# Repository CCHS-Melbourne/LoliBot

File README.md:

# LoliBot - The ESP32 Based Soccer bot.

Quick links ...

  * [Hardware assembly](http://www.openhardwareconf.org/wiki/LoliBot-Assembly)
  * [Software installation and usage](software)

Welcome to the 2018 linux.conf.au Open Hardware Project.  You can see information about this and other MiniConfs at <http://www.openhardwareconf.org/wiki/Main_Page>.

If you're attending the assembly workshop at Linux.conf.au 2018, the place to start is <http://www.openhardwareconf.org/wiki/LoliBot>

This year's project is called the Lolibot, and is a simple robot is designed to chase and kick a Ping Pong ball around.

It features a Lolin32-lite ESP32 based chip as it's primary microprocessor and includes a MPU6050 6 axis accelerometer.

In order to reduce complexity and to be a bit more flexible with our design this years project is a platform with discrete components.
Those of you who are looking forward to the smell of melting solder won't be disappointed though, there are many headers, LEDS and switches to keep you busy.

## Hardware

### Screen Shots

### Assembly

Assembly instructions for the kit are at <http://www.openhardwareconf.org/wiki/LoliBot-Assembly>

### Hardware Links

* [WEMOS LOLIN32](https://wiki.wemos.cc/products:lolin32:lolin32)
* [mpu-6050](https://www.invensense.com/products/motion-tracking/6-axis/mpu-6050/) TBD lots of options
* [Wheels](https://www.aliexpress.com/item/TT-Motor-130motor-with-the-wheel-Smart-Car-Robot-Gear-Motor-for-Arduino-DC3V-6V-DC/32829319427.html) one of many like this..

### datasheets

* [L9110 Motor control driver chip](datasheets/datasheet-l9110.pdf)

## Software

All the usual ESP32 development options apply to the LoliBot ...

 * [microPython scripts](software)
 * Arduino IDE sketches
 * Native ESP-IDF FreeRTOS firmware

We've chosen to focus on using microPython to provide a simple, yet
capable entry point for newcomers to robotics and embedded computers.

The [software sub-directory has instructions](software)
 on installing and developing software for the LoliBot.

## LICENSE

Licensed under the TAPR Open Hardware License (<http://www.tapr.org/OHL>). The "license" sub-folder also contains a copy of this license in plain text format.

Copyright John Spencer, Angus Gratton, Andy Gelme, Jon Oxer, Mark Wolfe 2017

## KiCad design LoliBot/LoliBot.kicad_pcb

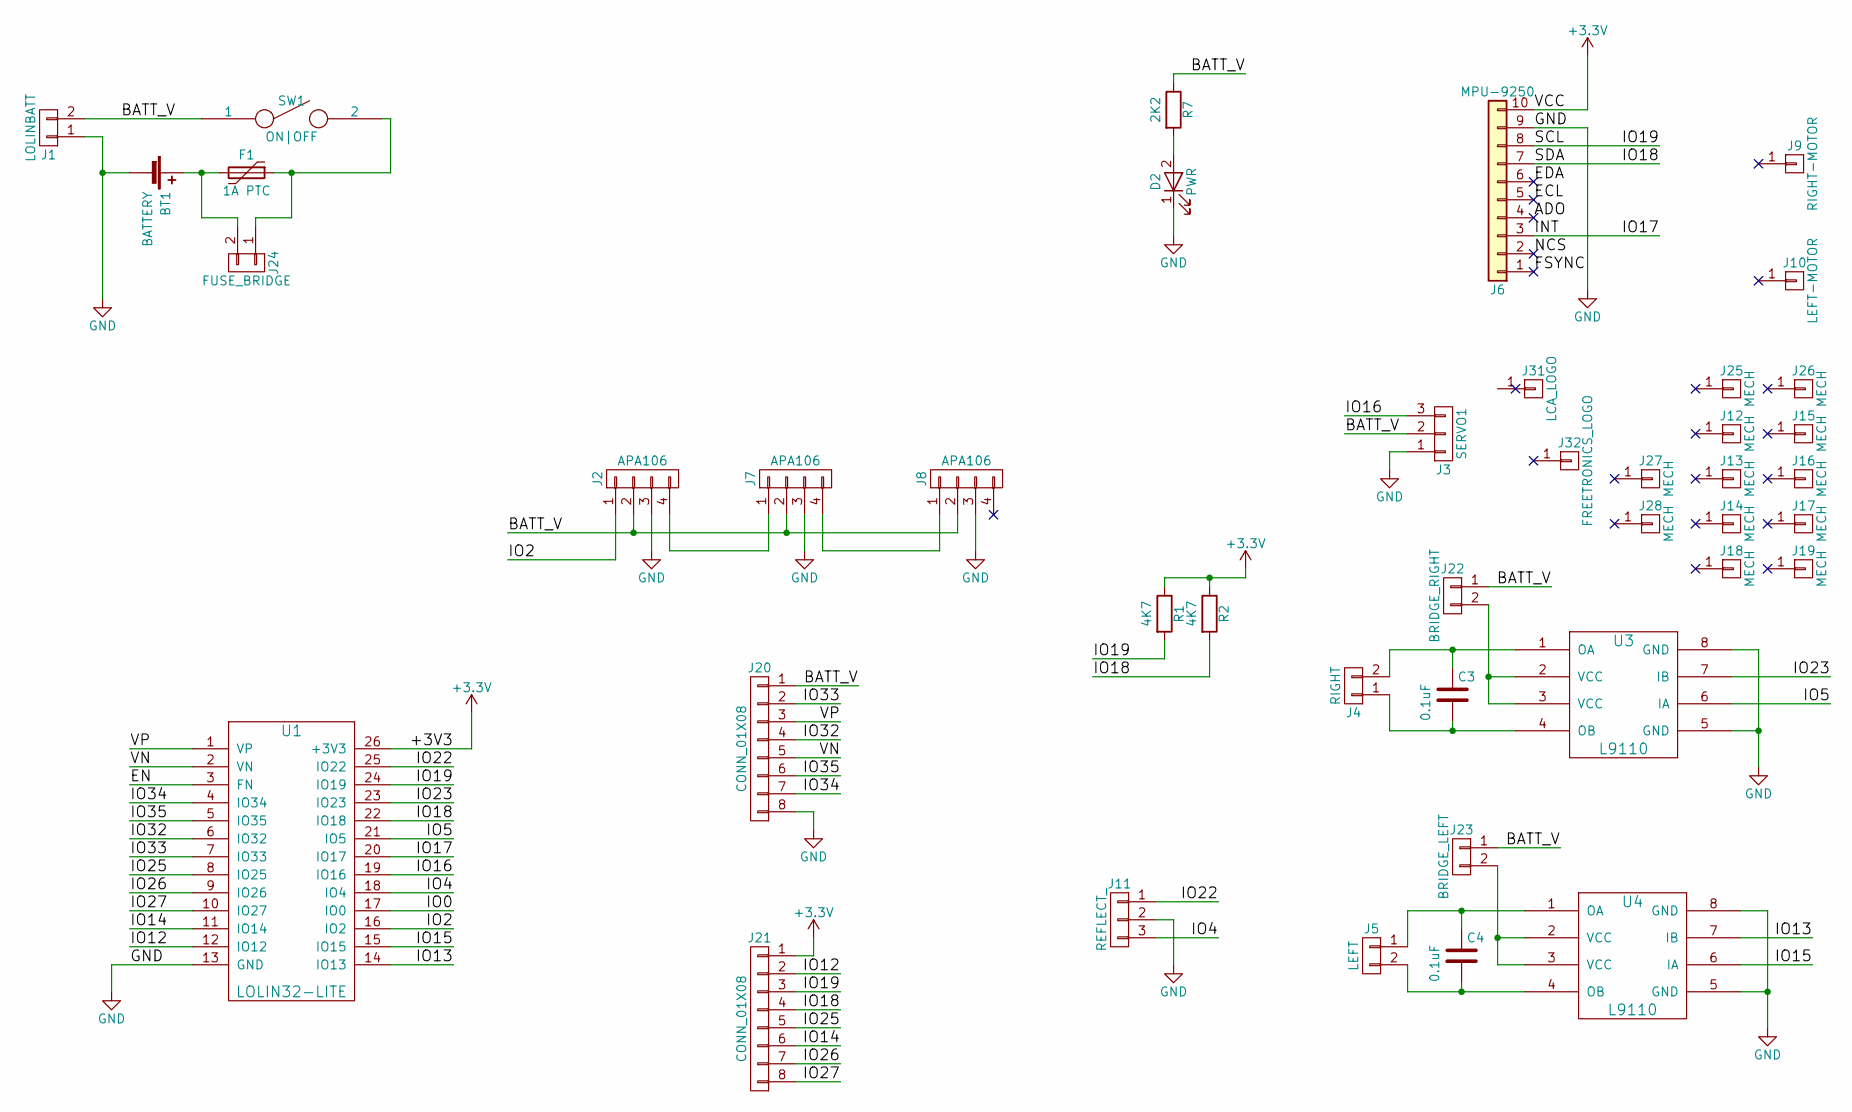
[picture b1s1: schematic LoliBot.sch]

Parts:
BT1: BATTERY; BH-18650
C3, C4: 0.1uF; C_0603_HandSoldering
D2: PWR; LED_D3.0mm
F1: 1A PTC; R_1210_HandSoldering
J1: LOLINBATT; Pin_Header_Straight_1x02_Pitch2.54mm
J2, J7, J8: APA106; LED_8MM_APA-106
J3: SERVO1; Pin_Header_Angled_1x03_Pitch2.54mm
J4: RIGHT; Pin_Header_Straight_1x02_Pitch2.00mm
J5: LEFT; Pin_Header_Straight_1x02_Pitch2.00mm
J6: MPU-9250; Pin_Header_Straight_1x10_Pitch2.54mm
J9: RIGHT-MOTOR; DC-Motor
J10: LEFT-MOTOR; DC-Motor
J11: REFLECT_; Pin_Header_Straight_1x03_Pitch2.54mm
J12, J13, J14, J15, J16, J17, J18, J19, J25, J26, J27, J28: MECH; MountingHole_3.2mm_M3_Pad
J20, J21: CONN_01X08; Pin_Header_Straight_2x04_Pitch2.54mm
J22: BRIDGE_RIGHT; Pin_Header_Straight_1x02_Pitch2.54mm
J23: BRIDGE_LEFT; Pin_Header_Straight_1x02_Pitch2.54mm
J24: FUSE_BRIDGE; bridge
J31: LCA_LOGO; LCA2018_LOGO
J32: FREETRONICS_LOGO; LOGO_FREETRONICS_33mm
R1, R2: 4K7; R_0603_HandSoldering
R7: 2K2; R_0603_HandSoldering
SW1: ON|OFF; SS12D00
U1: LOLIN32-LITE; lolin32-lite
U3, U4: L9110; SOIC-8_3.9x4.9mm_Pitch1.27mm

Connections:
+3V3: J6.10, J21.1, R1.1, R2.1, U1.26 (+3V3)
/ADO: J6.4
/BATT_V: J1.2, J2.2, J3.2, J7.2, J8.2, J20.1, J22.1, J23.1, R7.1, SW1.1
/ECL: J6.5
/EDA: J6.6
/EN: U1.3 (FN)
/FSYNC: J6.1
/INT: J6.3, U1.20 (IO17)
/IO0: U1.17 (IO0)
/IO2: J2.1, U1.16 (IO2)
/IO4: J11.3, U1.18 (IO4)
/IO5: U1.21 (IO5), U3.6 (IA)
/IO12: J21.2, U1.12 (IO12)
/IO13: U1.14 (IO13), U4.7 (IB)
/IO14: J21.6, U1.11 (IO14)
/IO15: U1.15 (IO15), U4.6 (IA)
/IO16: J3.3, U1.19 (IO16)
/IO18: J6.7, J21.4, R2.2, U1.22 (IO18)
/IO19: J6.8, J21.3, R1.2, U1.24 (IO19)
/IO22: J11.1, U1.25 (IO22)
/IO23: U1.23 (IO23), U3.7 (IB)
/IO25: J21.5, U1.8 (IO25)
/IO26: J21.7, U1.9 (IO26)
/IO27: J21.8, U1.10 (IO27)
/IO32: J20.4, U1.6 (IO32)
/IO33: J20.2, U1.7 (IO33)
/IO34: J20.7, U1.4 (IO34)
/IO35: J20.6, U1.5 (IO35)
/NCS: J6.2
/VN: J20.5, U1.2 (VN)
/VP: J20.3, U1.1 (VP)
GND: BT1.2 (-), D2.1 (K), J1.1, J2.3, J3.1, J6.9, J7.3, J8.3, J11.2, J20.8, U1.13 (GND), U3.5 (GND), U3.8 (GND), U4.5 (GND), U4.8 (GND)
unnamed: BT1.1 (+), F1.2, J24.2
unnamed: C3.1, J4.2, U3.1 (OA)
unnamed: C3.2, J4.1, U3.4 (OB)
unnamed: C4.1, J5.1, U4.1 (OA)
unnamed: C4.2, J5.2, U4.4 (OB)
unnamed: D2.2 (A), R7.2
unnamed: F1.1, J24.1, SW1.2
unnamed: J2.4, J7.1
unnamed: J7.4, J8.1
unnamed: J22.2, U3.2 (VCC), U3.3 (VCC)
unnamed: J23.2, U4.2 (VCC), U4.3 (VCC)

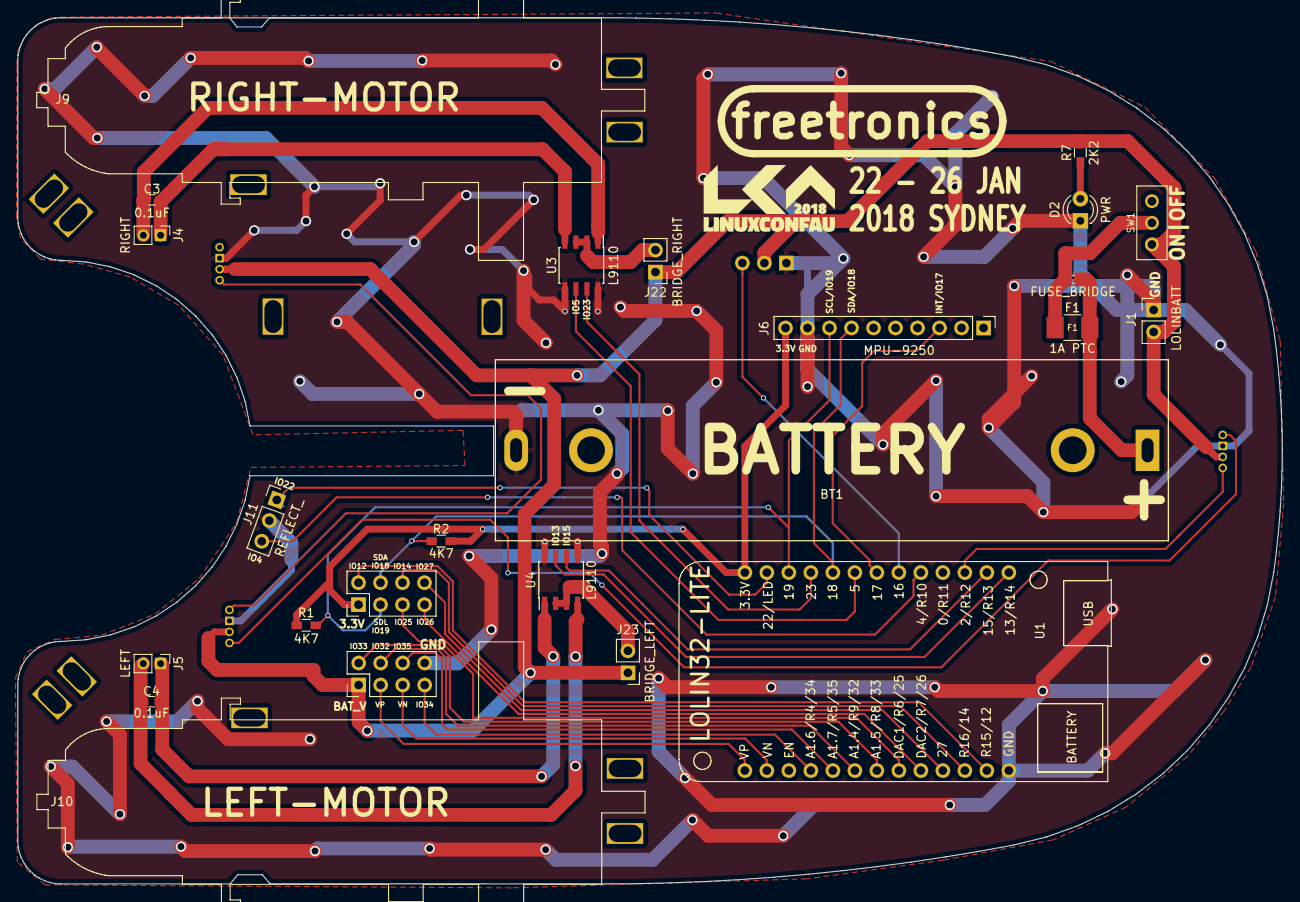
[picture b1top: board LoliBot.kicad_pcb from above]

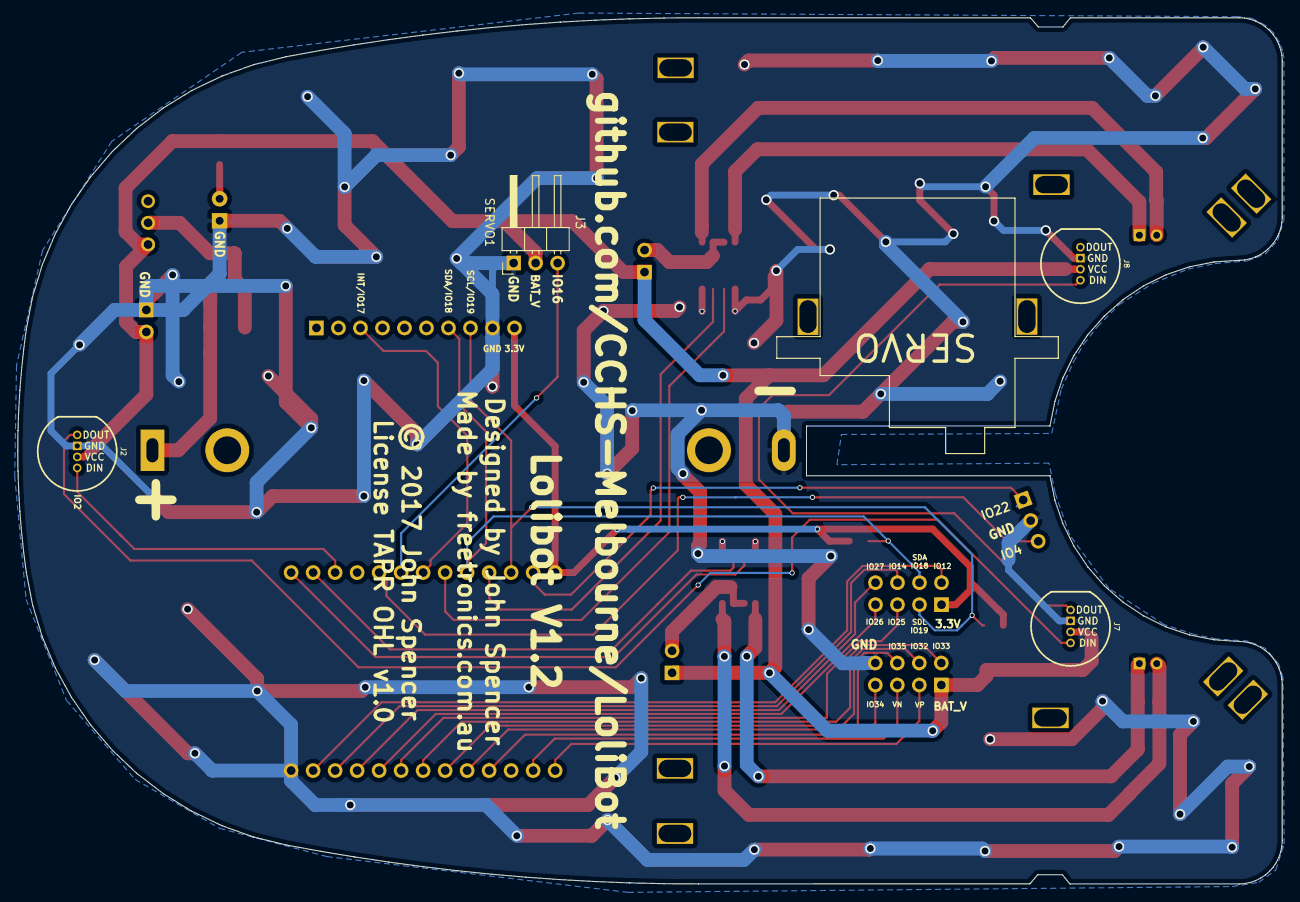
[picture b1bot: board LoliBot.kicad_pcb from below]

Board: 2 copper layers, 146.0 x 100.0 mm, 42 parts (4 on the bottom side), 36 nets.

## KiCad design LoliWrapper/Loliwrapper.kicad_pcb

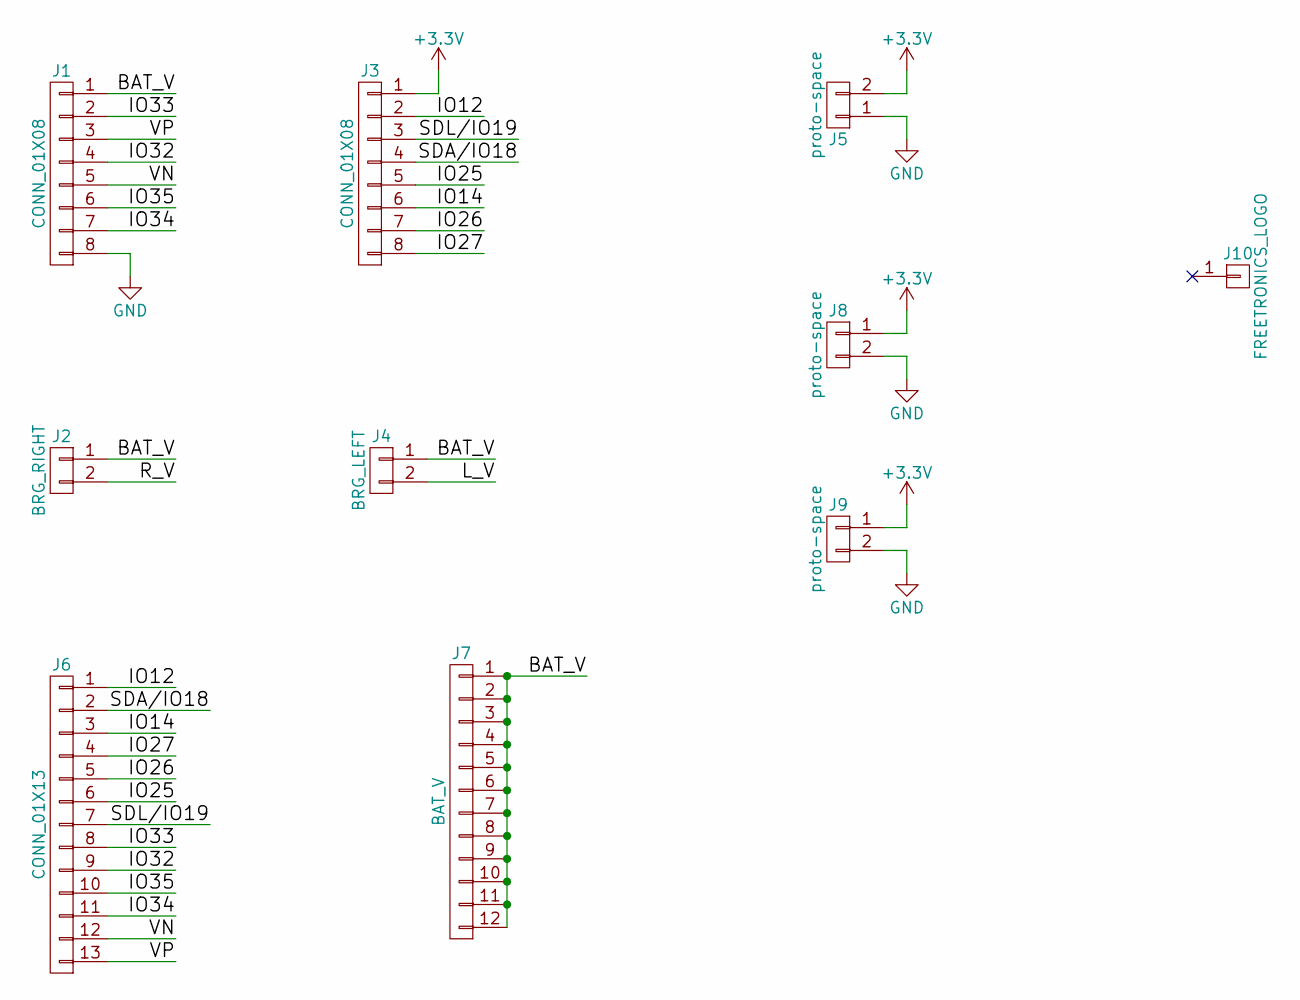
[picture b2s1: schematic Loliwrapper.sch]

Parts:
J1, J3: CONN_01X08; Pin_Header_Straight_2x04_Pitch2.54mm
J2: BRG_RIGHT; Pin_Header_Straight_1x02_Pitch2.54mm
J4: BRG_LEFT; Pin_Header_Straight_1x02_Pitch2.54mm
J5: proto-space; proto-board
J6: CONN_01X13; Pin_Header_Straight_1x13_Pitch2.54mm
J7: BAT_V; Pin_Header_Straight_1x12_Pitch2.54mm
J8: proto-space; 8x25-proto
J9: proto-space; 6x25-proto
J10: FREETRONICS_LOGO; LOGO_FREETRONICS_14mm

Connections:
+3V3: J3.1, J5.2, J8.1, J9.1
/BAT_V: J1.1, J2.1, J4.1, J7.1, J7.2, J7.3, J7.4, J7.5, J7.6, J7.7, J7.8, J7.9, J7.10, J7.11, J7.12
/IO12: J3.2, J6.1
/IO14: J3.6, J6.3
/IO25: J3.5, J6.6
/IO26: J3.7, J6.5
/IO27: J3.8, J6.4
/IO32: J1.4, J6.9
/IO33: J1.2, J6.8
/IO34: J1.7, J6.11
/IO35: J1.6, J6.10
/L_V: J4.2
/R_V: J2.2
/SDA/IO18: J3.4, J6.2
/SDL/IO19: J3.3, J6.7
/VN: J1.5, J6.12
/VP: J1.3, J6.13
GND: J1.8, J5.1, J8.2, J9.2

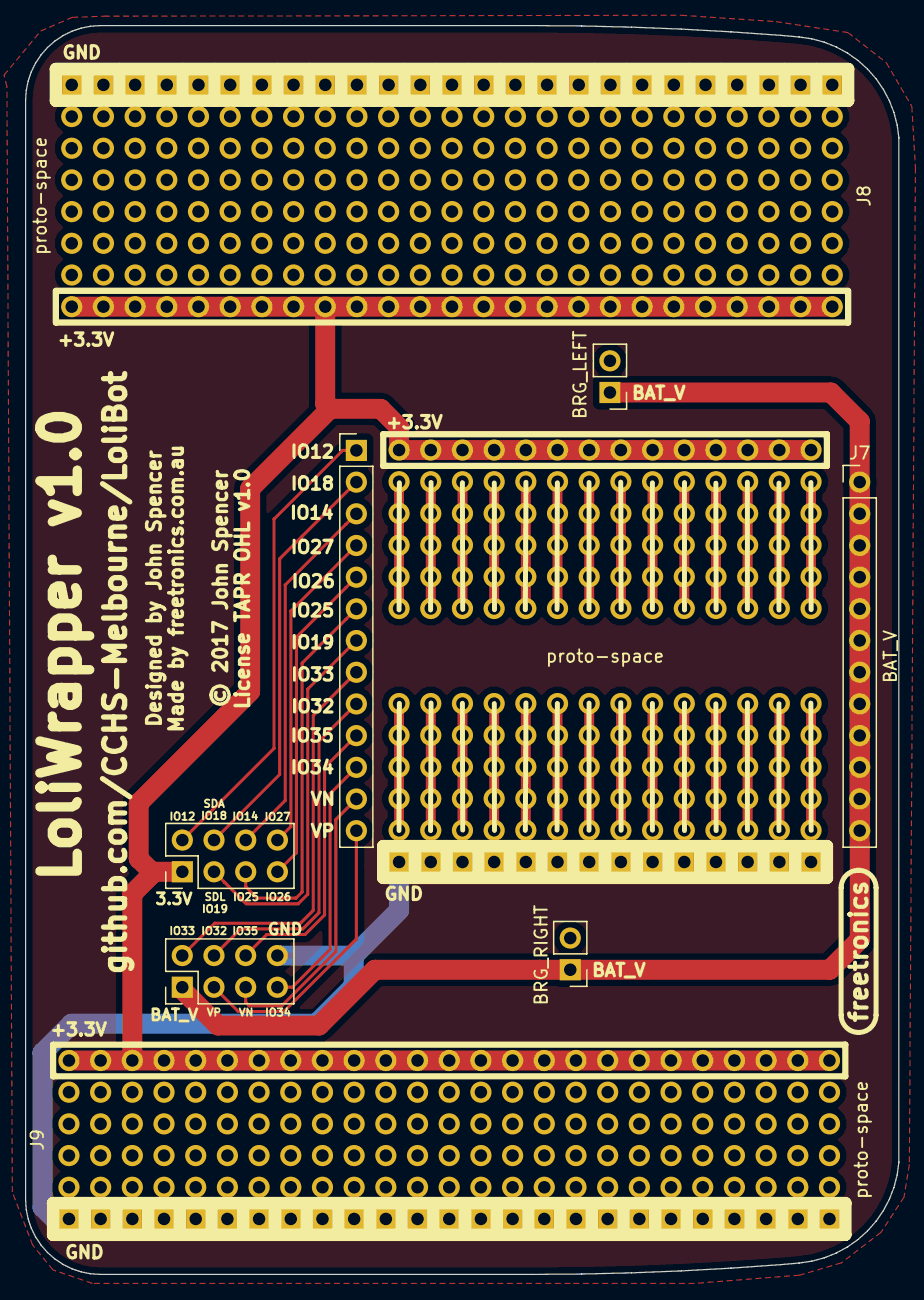
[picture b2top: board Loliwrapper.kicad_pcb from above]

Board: 2 copper layers, 70.0 x 100.1 mm, 10 parts (0 on the bottom side), 16 nets.

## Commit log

2017-10-05 Initial starting point.
2017-10-09 Added rough concept in Eagle format
2017-10-09 Added PCB preview in PDF
2017-10-09 Created KiCAD Schematic
2017-10-10 feat(Layout) Added slots and drill holes based on the existing DXF
2017-10-11 Added 3d model of mock up.
2017-10-12 Added Battery Footprint
2017-10-13 Added footprint for lolibot-lite
2017-10-15 Added mpu-9250 module header and updated power pins.
    * Fixes to the l9110 library for power input
    * Fixes to the lolin32-lite library for power output
2017-10-15 Assigned some footprints and built out apa106 chain for underlights.
2017-10-15 Added datasheets and started assigning footprints.
2017-10-25 Added footprints
2017-10-25 Added Board for JS Version
2017-10-26 Updated lolin32-lite footprint
2017-11-01 Added Mounting brackets and IR sensor
2017-11-12 Updated footprint
    Improved motor driver positions.
    Rotated acel to match x/y directions
2017-11-16 Whoops, those L9110 Pins don't go there.
2017-11-17 Pin reassignment.
2017-11-20 Added expansion ports
2017-11-20 Moved Servo position
    to remove interference with expansion ports.
2017-11-20 Added Schematic PDF
2017-11-22 battery symbols reversed.
2017-11-26 Removed voltage boost.
2017-11-26 Updated renders
2017-11-30 wrong image. every damn time.
2017-12-07 Added Fuse. Updated pcb
2017-12-07 Added Through holes for cable ties
2017-12-10 Started silkscreen
2017-12-11 Added logos and text
    And vias.
2017-12-11 Added more text
2017-12-12 i2c pullup resistors
2017-12-13 Eagle files and datasheet removed
    To maintain consistency. The Eagle version is now out of date.
2017-12-13 Updated render link
2017-12-15 Final update for version 1.2
2017-12-19 Moved circuit locations
2017-12-19 Added LoliWrapper
2017-12-19 updated silkscreen
2017-12-20 fixed overhanging through holes.
    Board production house didn't like vias that get cut in half
2018-01-14 Initial LoliBot microPython software check-in.
2018-01-15 Temporarily hide "script/flash_lolibot.sh" failure to remove "boot.py".
2018-01-15 Correctly calculate 2D to 1D coordinates based on X-axis size.
2018-01-16 Move "configuration/wifi.py" to "configuration/wifi.py.template" and added ".gitignore" file.
2018-01-20 README.md: Update with some links to the OHMC2018 wiki
2018-01-20 Updated "flash_lolibot.sh" to use latest firmware.
2018-01-20 Initial documentation outline.
2018-01-20 Minor improvements to the main page link to the software instructions.
2018-01-20 Some quick links to useful information.
2018-01-20 Added instructions for Python and PIP installation.
2018-01-21 Added instructions for USB serial driver installation.
2018-01-21 Minor "software/ReadMe.md" improvements.
2018-01-21 Highlighting !
2018-01-21 Fix broken integer to string cast got motor frequency MQTT command.
2018-01-21 Completed development (host) computer software installation.
2018-01-21 Completed Wi-Fi configuration documentation.
2018-01-21 Completed MQTT configuration documentation.
2018-01-21 Some minor ReadMe.md improvements.
2018-01-22 Place a note against temporarily dead links.
2018-01-22 explain how to install and use pip3 on debian
2018-01-22 silly little interactive controller
2018-01-22 software/scripts: Split firmware flash and micropython update
    Add a 2nd script to update the micropython code separately from
    reflashing the firmware image
2018-01-22 mqtt: Catch exceptions in message handlers
    If a message handler throws an except because of some
    malformed input, catch it rather than letting it kill
    the main loop and dropping to a REPL.
2018-01-22 mqtt: Publish to the 'state' topic when booted
    Announce our existence to the world, making it easier
    to see which bots are alive
2018-01-22 Create I2C bus in the lolibot module
2018-01-22 mpu9250: Convert line endings to unix
2018-01-22 mpu9250: Basic accelerometer support
    Initialise the accelerometer, and once per second
    output the maximum / minimum reading. Needs hooking
    up to MQTT and other stuff
2018-01-22 mpu9250: Handle module not being installed gracefully
    Don't complain or print empty output if the accelerometer
    module is not installed
2018-01-22 Lolibot: Add 'servo' and 'motors' commands
    Support directly settings motor PWM controls
    motors (1023 0 1023 0) to go forward
    Support servo command 'servo [-100..100] for -100
    (backward spin) to 100 (forward spin) and 0 for stop
2018-01-22 Add link to OHMC LoliBot Software Presentation.
2018-01-22 MQTT via WebSocket example controller
2018-01-22 lolibot: Check the motors command comes with 4 args
2018-01-22 udp_control: Add a listener on port 4900 for control
    Receive commands with the same format as the MQTT
    endpoint directly on port 4900.
    Periodically sends a broadcast presence announcement
    to the network on that port too
2018-01-22 windows flash_lolibot script
2018-01-22 examples/controller.sh: default to stop
    Make any input that is not registered default to stop.
2018-01-22 examples/controller.sh: make sure we stop when exiting
    Add an exit trap so regardless of how the script is terminated
    the LoliBot will stop.
2018-01-22 examples/controller.sh: lookup the MQTT host from the configuration
    Saves having to update the MQTT host in multiple places.
2018-01-22 Removed dead links.

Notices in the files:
Eagle/LoliBot.sch:
(C) 2017 Freetronics Pty Ltd
Released under the TAPR Open Hardware License: tapr.org/ohl
LoliBot/LoliBot.kicad_pcb:
© 2017 John Spencer
parts and their libraries:
freetronics-original: Licensing: CC v3.0 Share-Alike You are welcome to use this library for commercial purposes.
